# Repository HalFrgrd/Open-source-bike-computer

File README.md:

# Open source-bike-computer
Designs for an open source bike computer.

Similar projects:
- https://github.com/vincent290587/stravaV10
- http://opencyclingcomputer.eu/
- https://gitlab.com/PrzemoF/Open-Cycling-Computer
- https://github.com/hishizuka/pizero_bikecomputer

## BOM

<!--  -->
<!-- |---|---|---|---|---| -->
<!-- |**Preassembled** T-Call v1.3 TTGO ESP32 (no GPS)   | 29 x 7 x 8mm   | $16  | No  |   | -->

||**Item**   | **Dimensions**   | **Cost**  | **Using**  |   |
|---|---|---|---|---|---|
|**Display**|
|| |    | $13   | Yes  |   |
|**Battery and charging**|
||3.7v Lithium Polymer 3200mAh   | 50 x 75 x 7mm  | $8.50  | Yes  |   |
||Receiver pad | 0.5mm thick  | $3  | Yes  |   |
||Charging base  |  | $4  | Yes  |   |
| **Storage** |
||16gb micro SD card   |   | $5  | Yes   |   |
|**Microcontroller and modules** |
||  ESP32 with LiPo charging  |   | $5  | Yes  |   |
|| nrf52840| |$5| Yes||
||  GPS module   |   | $5  | Yes  |   |
||  SIM800L module   |   | $4  | Yes  |   |
|| Micro SD card module  |   | $1  | Yes  |   |
|**Case**|
|| Glass screen protector | | $2 | Yes | |
|| 3D printed enclosure | |  | Yes | |
|| Glue | |  | Yes | |
|| 4 mounting screws | |  | Yes | |
|| 4 threaded heat inserts | |  | Yes | |
|| Rubber o-ring cabling | |  | Yes | |
| **Total** | | | | |

### Actually buying:

[LS027B7DH01](https://www.aliexpress.com/item/33020027250.html?spm=a2g0o.productlist.0.0.36ee3a15mb1GMf&algo_pvid=aad3c1d1-297e-4d29-b040-a34f9ef8f99c&algo_expid=aad3c1d1-297e-4d29-b040-a34f9ef8f99c-1&btsid=0b0a119a15935113972186751eb958&ws_ab_test=searchweb0_0,searchweb201602_,searchweb201603_)
The A indicates maximum of two bright pixels. 
Need an FPC 10 pin connector

## Design

3D printed

The buttons are capacitive pads. 
These pads will be a separate PCB that you can glue onto the 3D printed case.
This will be a water proof seal.
Will the capacitive pads be sensitive to rain?

Maximum target dimensions: 55 wide, 80 long, 20 high 

Need the on off control and charging port to be water proof.

### Capacitive buttons:
ESP32 has 10 capacitive-sensing GPIOs. 
So you don't need to include any extra components to use capacitive buttons
The nrf52 series also don't require any external componenents.

The capacitive pads could perhaps also go under the screen protector.
I'm guessing a screen protector wouldn't reduce the touch sensitivity that much.
This would serve as protection for the capacitive pads.

It is important to reduce the parasitic capacitance and increase the touch capacitance.
How to optimize: reduce trace length by optimizing PCB layout; reduce thickness of the overlay; enlarge electrode's area. 
Could have surface mount pins to reach PCB below.

https://github.com/espressif/esp-iot-solution/blob/master/documents/touch_pad_solution/touch_sensor_design_en.md

https://www.embedded.com/making-capacitive-touch-sensors-water-tolerant/

https://devzone.nordicsemi.com/nordic/short-range-guides/b/design-examples/posts/capacitive-touch-on-the-nrf52-series
### Firmware
https://www.youtube.com/watch?v=lQ157ftTnSs

Google maps platform has a $200 free monthly usage. Could use their route planning.

### Display
[2.42" OLED](https://www.aliexpress.com/item/32950562791.html?spm=a2g0o.productlist.0.0.4f122c2fbCw4XX&algo_pvid=e3eca0d5-b70e-4a4d-96aa-446986a5b739&algo_expid=e3eca0d5-b70e-4a4d-96aa-446986a5b739-2&btsid=0b0a050115931950007767265e4fd4&ws_ab_test=searchweb0_0,searchweb201602_,searchweb201603_)
Not the best choice since they compete with sunlight.

Reflective LCD

https://www.buydisplay.com/blog/what-are-the-main-differences-between-LCD-and-OLED.html

https://www.buydisplay.com/3-4-inch-graphic-touchscreen-lcd-cog-module-240x160-single-sided-fpc
https://www.buydisplay.com/3-inch-touch-240x120-graphic-displays-lcd-serial-interface-black-on-white

https://forum.arduino.cc/index.php?topic=188040.0
https://forum.arduino.cc/index.php?topic=488097.0
https://forum.arduino.cc/index.php?topic=554754.0

Vincent's stravaV10 uses Memory LCD LS027B7DH01
https://makerdyne.com/2015/02/08/large-memory-lcd-breakout-board-details/
https://makerdyne.files.wordpress.com/2015/12/MemoryLCD_Breakout_Board_Schematic.pdf

The LS027B7DH01 with a backlight by Flex:
https://www.digikey.com/products/en?mpart=11103-06_T5&v=2004

### Wireless charging
This both for convenience and keeping the enclosure waterproof. 
Quite cheap for a whole setup. The pad inside of the computer can be very slim.

This one is small enough to be away from antennas.
https://www.mouser.co.uk/ProductDetail/PulseLarsen-Antennas/WMRR124F-2?qs=w%2Fv1CP2dgqrPY4DsgoYlEg%3D%3D

### Contactless payment
https://www.instructables.com/id/RFID-NFC-Tap-and-Go-Ring-for-Credit-Card-Payment/

Could just have a thin slot for a pay as you go card (Revolut or Monzo).Could have SMS notifications so that the bike computer knows when you have paid. 
Set up that sim with that bank card.
Could acetone the bank card to make it slimmer.

### SIM
https://lastminuteengineers.com/sim800l-gsm-module-arduino-tutorial/
I hope to be able to use the microphone pins to play pre-recorded messages.

### PCB design

Pin choice: It seems like the nrf52840 are pretty multi-purpose. For high-frequency stuff, try and avoid pins close to the antenna to avoid interference.
https://devzone.nordicsemi.com/f/nordic-q-a/52857/recommended-pin-usage

P0.0 = 0, P0.1 = 1 .... P0.31 = 31 P1.0 = 32, P1.1 = 33. 

Sharp memory schematics:
https://makerdyne.files.wordpress.com/2015/12/MemoryLCD_Breakout_Board_Schematic.pdf

One set of SPI pins per peripheral: they might work at different speeds. And I think the asynchronous aspect would mean the LCD could be prioritized.

https://github.com/DF4IAH/HFT-Core-Module

Antenna:
SIM868 is L1 band.
Glonass L1: about 1602 MHz
GPS L1: 1575.42 MHz
Beidou: 1575.42 MHz (Possibly lower: 1561.098MHz?)

https://www.antenova.com/integration-hub/antenna-selection-tool/

Drawing antennas as part of the PCB seem like a bad idea. 
They take a lot of testing.

Mouser sells the SR4L049 (both left and right versions) for about 3 dollars. SR4L034 is very similar.

The M20057 and M20047 modules combine the SAW and antenna. Power consumption is about 2ma,

M20047 cost: 4.50 gbp from mouser and at digikey
B3913 cost: 1.62gbp 
SR4L034 cost: 1.44
LNA?:

I'm pretty sure it needs an LNA. So I'm going with 
https://www.u-blox.com/sites/default/files/NEO-8Q-NEO-M8-FW3_HIM_%28UBX-15029985%29.pdf

[Picking a saw filter from Mouser](https://www.mouser.com/pdfdocs/HowToChoosetheOptimalSAWFilter.pdf)

SAW filter: You want something in the middle of the frequencies, so 1588ish and that has a wide enough bandwidth to capture the signals.
Two come up: B3913 and B3413. The B4310 is used in the HFT-Core-Module.
B4310 is from 2015. The B3913 and B3413 are very similar but the B3413 is newer and has improved electrostatic discharge (ESD) robustness. [Qualcomm RF360 website SAW filters for GNSS](https://rffe.qualcomm.com/product/search/automotive/Filters%20for%20GNSS). B4310 doesn't have Beidou next to it on the website. 
I can't find the B3413 in stock, so I'm using the B3913 in stock at digi key.

#### Questions
- The wireless charging setup.
- Battery level indicator.
- Why polarized capacitor in decoupling?
- RF SYNC
- What about low noise ammplifer LNA?

### Case
**Two pcb design**
Have a pcb at the top. 
This has a cut out for the screen.
This top pcb has capacitive buttons.
On the underside of this top pcb, are an on off switch and maybe the usb port. Also could have pressure, temperature, humidity sensor as it should be on the outside? The traces are the link between the outside and the inside.
The 3D printed bottom port of the case could just be unibody.
There would be pcb to pcb connectors.
The top pcb would have surface mounted pins on the underside.
The bottom pcb would have the female connectors.
When you align the pins, the top pcb drops into the bottom one.
[These are pin and socket](https://blog.samtec.com/post/custom-connectors-for-stacking-pcbs/)
There would be o-rings around each of the mounting screws and o-ring cord going around the perimeter.

The two PCBs could fit together inside the 100x100mm size.

Could this extend the ground plane?:
https://blog.antenova.com/how-well-can-an-embedded-antenna-perform-on-a-tiny-pcb

Threaded PCB inserts could provide a flush mounting style.

Connections between plates:
- Ground
- VCC
- Battery switch
- Data+
- Data -
- 5x buttons
- Temperature, pressure, humidity sensor.

Connectors: https://www.samtec.com/products/ftsh

Pins:FTSH-104-01-F-DV
Connector: CLP-104-02-F-D

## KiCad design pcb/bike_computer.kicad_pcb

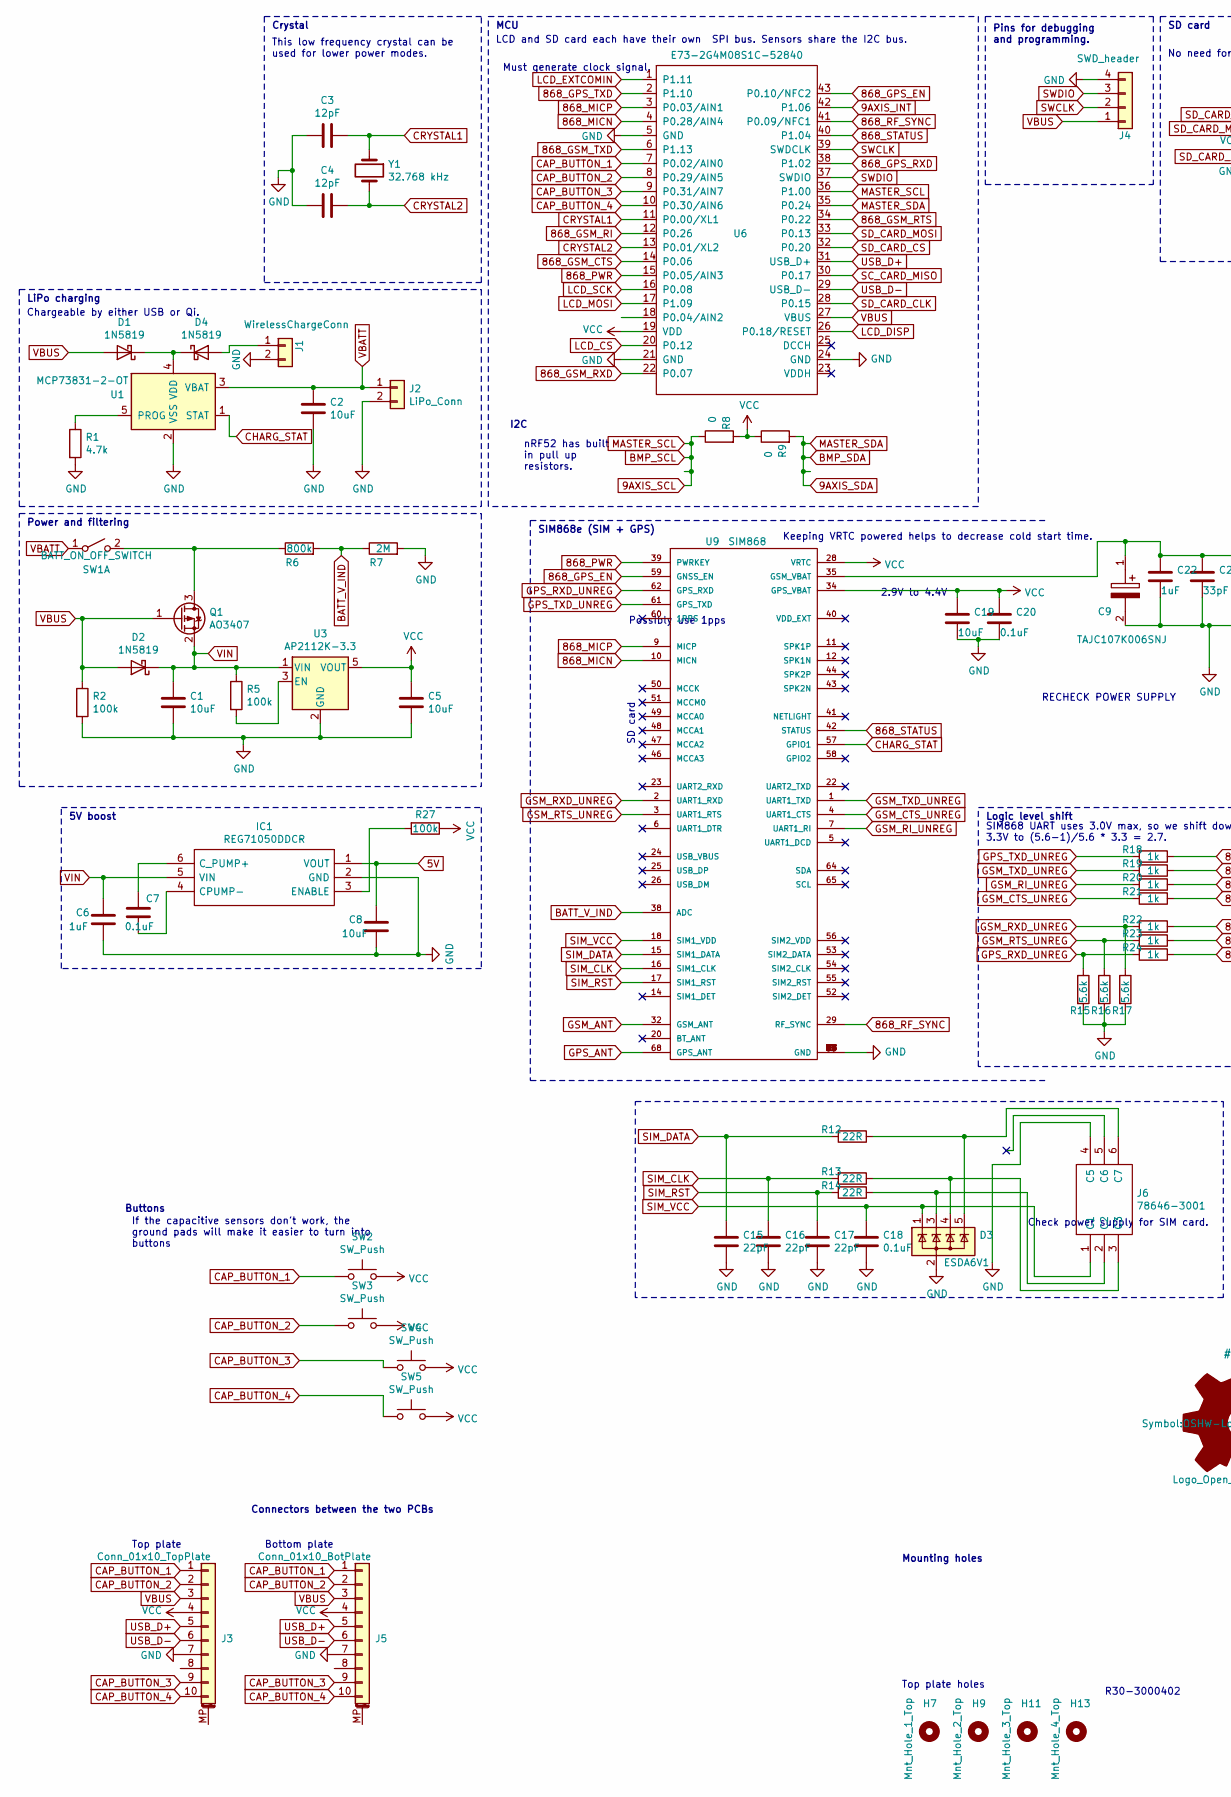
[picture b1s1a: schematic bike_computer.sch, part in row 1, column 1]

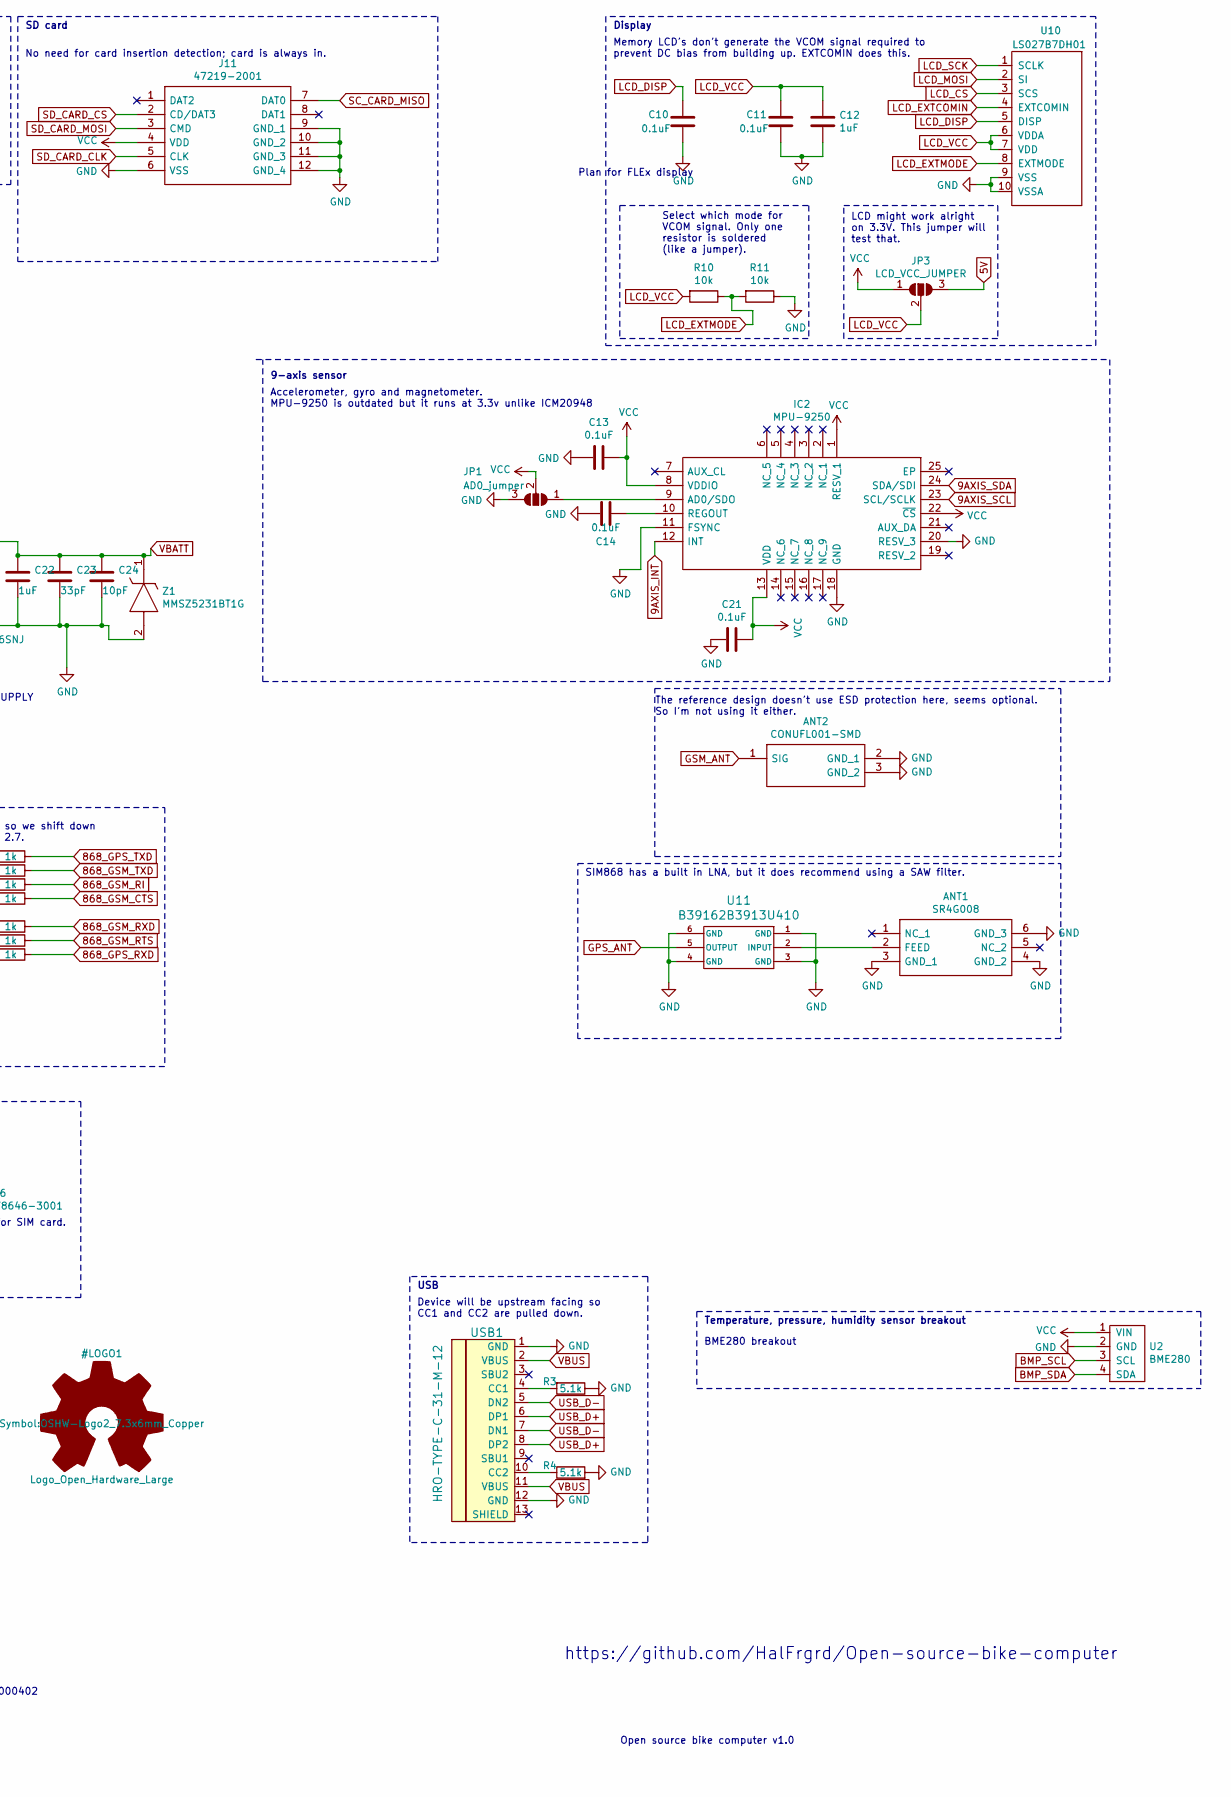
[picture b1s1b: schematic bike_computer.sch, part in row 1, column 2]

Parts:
ANT1: SR4G008; Mouser Part Number 237-SR4G008
ANT2: CONUFL001-SMD; Mouser Part Number 712-CONUFL001-SMD
C1, C2, C5, C8, C19: 10uF; 1206_0603_hand_solder
C3, C4: 12pF; 1206_0603_hand_solder
C6, C12, C22: 1uF; 1206_0603_hand_solder
C7, C10, C11, C13, C14, C18, C20, C21: 0.1uF; 1206_0603_hand_solder
C9: TAJC107K006SNJ; CAPPM6032X280N; Mouser Part Number 581-TAJC107K006SNJ
C15, C16, C17: 22pF; 1206_0603_hand_solder
C23: 33pF; 1206_0603_hand_solder
C24: 10pF; 1206_0603_hand_solder
D1, D2, D4: 1N5819; D_SOD-123
D3: ESDA6V1; SOT95P280X145-6N
H7: Mnt_Hole_1_Top; R303000402
H9: Mnt_Hole_2_Top; R303000402
H11: Mnt_Hole_3_Top; R303000402
H13: Mnt_Hole_4_Top; R303000402
IC1: REG71050DDCR; SOT95P280X110-6N; Mouser Part Number 595-REG71050DDCR
IC2: MPU-9250; QFN40P300X300X105-25N-D; Mouser Part Number 410-MPU-9250
J1: WirelessChargeConn; PinHeader_1x02_P1.27mm_Vertical
J2: LiPo_Conn; PinHeader_1x02_P1.27mm_Vertical
J3: Conn_01x10_TopPlate; 10_smd_connector
J4: SWD_header; PinHeader_1x04_P2.54mm_Vertical
J5: Conn_01x10_BotPlate; PinHeader_1x10_P2.54mm_Vertical
J6: 78646-3001; Mouser Part Number 538-78646-3001
J11: 47219-2001; 472192001; Mouser Part Number 538-47219-2001
JP1: AD0_jumper; SolderJumper-3_P1.3mm_Open_RoundedPad1.0x1.5mm
JP3: LCD_VCC_JUMPER; SolderJumper-3_P1.3mm_Open_RoundedPad1.0x1.5mm
Q1: AO3407; SOT-23
R1: 4.7k; 1206_0603_hand_solder
R2, R5, R27: 100k; 1206_0603_hand_solder
R3, R4: 5.1k; 1206_0603_hand_solder
R6: 800k; 1206_0603_hand_solder
R7: 2M; 1206_0603_hand_solder
R8, R9: 0; 1206_0603_hand_solder
R10, R11: 10k; 1206_0603_hand_solder
R12, R13, R14: 22R; 1206_0603_hand_solder
R15, R16, R17: 5.6k; 1206_0603_hand_solder
R18, R19, R20, R21, R22, R23, R24: 1k; 1206_0603_hand_solder
SW1: BATT_ON_OFF_SWITCH; switch_MSK-12C02_smd
SW2, SW3, SW4, SW5: SW_Push; KSC521JROHS_with_pad
U1: MCP73831-2-OT; SOT-23-5
U2: BME280
U3: AP2112K-3.3; SOT-23-5
U6: E73-2G4M08S1C-52840
U9: SIM868; XCVR_SIM868
U10: LS027B7DH01; TE_1-1734839-0_1x10-1MP_P0.5mm_Horizontal
U11: B39162B3913U410
USB1: HRO-TYPE-C-31-M-12
Y1: 32.768 kHz; Crystal_DS26_D2.0mm_L6.0mm_Horizontal
Z1: MMSZ5231BT1G; SOD3716X135N; Mouser Part Number 863-MMSZ5231BT1G

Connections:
5V: C8.1, IC1.1 (VOUT), JP3.3 (B)
9AXIS_INT: IC2.12 (INT), U6.42 (P1.06)
9AXIS_SCL: IC2.23 (SCL/SCLK), R8.1, U2.3 (SCL), U6.36 (P1.00)
9AXIS_SDA: IC2.24 (SDA/SDI), R9.2, U2.4 (SDA), U6.35 (P0.24)
868_GPS_EN: U6.43 (P0.10/NFC2), U9.59 (GNSS_EN)
868_GPS_RXD: R24.1, U6.38 (P1.02)
868_GPS_TXD: R18.1, U6.2 (P1.10)
868_GSM_CTS: R21.1, U6.14 (P0.06)
868_GSM_RI: R20.1, U6.12 (P0.26)
868_GSM_RTS: R23.1, U6.34 (P0.22)
868_GSM_RXD: R22.1, U6.22 (P0.07)
868_GSM_TXD: R19.1, U6.6 (P1.13)
868_MICN: U6.4 (P0.28/AIN4), U9.10 (MICN)
868_MICP: U6.3 (P0.03/AIN1), U9.9 (MICP)
868_PWR: U6.15 (P0.05/AIN3), U9.39 (PWRKEY)
868_RF_SYNC: U6.41 (P0.09/NFC1), U9.29 (RF_SYNC)
868_STATUS: U6.40 (P1.04), U9.42 (STATUS)
BATT_V_IND: R6.2, R7.1, U9.38 (ADC)
CAP_BUTTON_1: J3.1, J5.1, SW2.1, U6.7 (P0.02/AIN0)
CAP_BUTTON_2: J3.2, J5.2, SW3.1, U6.8 (P0.29/AIN5)
CAP_BUTTON_3: J3.9, J5.9, SW4.1, U6.9 (P0.31/AIN7)
CAP_BUTTON_4: J3.10, J5.10, SW5.1, U6.10 (P0.30/AIN6)
CHARG_STAT: U1.1 (STAT), U9.57 (GPIO1)
CRYSTAL1: C3.1, U6.11 (P0.00/XL1), Y1.1
CRYSTAL2: C4.1, U6.13 (P0.01/XL2), Y1.2
GND: ANT1.3 (GND_1), ANT1.4 (GND_2), ANT1.6 (GND_3), ANT2.2 (GND_1), ANT2.3 (GND_2), C1.2, C2.2, C3.2, C4.2, C5.2, C6.2, C8.2, C9.2, C10.2, C11.2, C12.2, C13.2, C14.1, C15.2, C16.2, C17.2, C18.2, C19.2, C20.2, C21.2, C22.2, C23.2, C24.2, D3.2 (A), IC1.2 (GND), IC2.11 (FSYNC), IC2.18 (GND), IC2.20 (RESV_3), J1.2, J2.2, J3.7, J4.4, J5.7, J6.4 (C5), J11.6 (VSS), J11.9 (GND_1), J11.10 (GND_2), J11.11 (GND_3), J11.12 (GND_4), JP1.3 (B), R1.2, R2.2, R3.1, R4.2, R7.2, R11.1, R15.2, R16.2, R17.2, U1.2 (VSS), U2.2 (GND), U3.2 (GND), U6.5 (GND), U6.21 (GND), U6.24 (GND), U9.8 (GND), U9.13 (GND), U9.19 (GND), U9.21 (GND), U9.27 (GND), U9.30 (GND), U9.31 (GND), U9.33 (GND), U9.36 (GND), U9.37 (GND), U9.45 (GND), U9.63 (GND), U9.66 (GND), U9.67 (GND), U9.69 (GND), U9.70 (GND), U9.71 (GND), U9.72 (GND), U9.73 (GND), U9.74 (GND), U9.75 (GND), U9.76 (GND), U9.77 (GND), U10.9 (VSS), U10.10 (VSSA), U11.1 (GND), U11.3 (GND), U11.4 (GND), U11.6 (GND), USB1.1 (GND), USB1.12 (GND), Z1.2
GPS_ANT: U9.68 (GPS_ANT), U11.5 (OUTPUT)
GPS_RXD_UNREG: R15.1, R24.2, U9.62 (GPS_RXD)
GPS_TXD_UNREG: R18.2, U9.61 (GPS_TXD)
GSM_ANT: ANT2.1 (SIG), U9.32 (GSM_ANT)
GSM_CTS_UNREG: R21.2, U9.4 (UART1_CTS)
GSM_RI_UNREG: R20.2, U9.7 (UART1_RI)
GSM_RTS_UNREG: R16.1, R23.2, U9.3 (UART1_RTS)
GSM_RXD_UNREG: R17.1, R22.2, U9.2 (UART1_RXD)
GSM_TXD_UNREG: R19.2, U9.1 (UART1_TXD)
LCD_CS: U6.20 (P0.12), U10.3 (SCS)
LCD_DISP: C10.1, U6.26 (P0.18/RESET), U10.5 (DISP)
LCD_EXTCOMIN: U6.1 (P1.11), U10.4 (EXTCOMIN)
LCD_EXTMODE: R10.1, R11.2, U10.8 (EXTMODE)
LCD_MOSI: U6.17 (P1.09), U10.2 (SI)
LCD_SCK: U6.16 (P0.08), U10.1 (SCLK)
LCD_VCC: C11.1, C12.1, JP3.2 (C), R10.2, U10.6 (VDDA), U10.7 (VDD)
unnamed: ANT1.2 (FEED), U11.2 (INPUT)
unnamed: C7.1, IC1.6 (C_PUMP+)
unnamed: C7.2, IC1.4 (CPUMP-)
unnamed: C14.2, IC2.10 (REGOUT)
unnamed: D1.1 (K), D4.1 (K), U1.4 (VDD)
unnamed: D3.3 (K), J6.2 (C2), R14.1
unnamed: D3.4 (K), J6.3 (C3), R13.1
unnamed: D3.5 (K), J6.6 (C7), R12.1
unnamed: D4.2 (A), J1.1
unnamed: IC1.3 (ENABLE), R27.2
unnamed: IC2.9 (AD0/SDO), JP1.1 (A)
unnamed: Q1.3 (D), R6.1, SW1.2 (B)
unnamed: R1.1, U1.5 (PROG)
unnamed: R3.2, USB1.4 (CC1)
unnamed: R4.1, USB1.10 (CC2)
unnamed: R5.2, U3.3 (EN)
SC_CARD_MISO: J11.7 (DAT0), U6.30 (P0.17)
SD_CARD_CLK: J11.5 (CLK), U6.28 (P0.15)
SD_CARD_CS: J11.2 (CD/DAT3), U6.32 (P0.20)
SD_CARD_MOSI: J11.3 (CMD), U6.33 (P0.13)
SIM_CLK: C16.1, R13.2, U9.16 (SIM1_CLK)
SIM_DATA: C15.1, R12.2, U9.15 (SIM1_DATA)
SIM_RST: C17.1, R14.2, U9.17 (SIM1_RST)
SIM_VCC: C18.1, D3.1 (K), J6.1 (C1), U9.18 (SIM1_VDD)
SWCLK: J4.2, U6.39 (SWDCLK)
SWDIO: J4.3, U6.37 (SWDIO)
USB_D+: J3.5, J5.5, U6.31 (USB_D+), USB1.6 (DP1), USB1.8 (DP2)
USB_D-: J3.6, J5.6, U6.29 (USB_D-), USB1.5 (DN2), USB1.7 (DN1)
VBATT: C2.1, C9.1, C22.1, C23.1, C24.1, J2.1, SW1.1 (A), U1.3 (VBAT), U9.35 (GSM_VBAT), Z1.1
VBUS: D1.2 (A), D2.2 (A), J3.3, J4.1, J5.3, Q1.1 (G), R2.1, U6.27 (VBUS), USB1.2 (VBUS), USB1.11 (VBUS)
VCC: C5.1, C13.1, C19.1, C20.1, C21.1, IC2.1 (RESV_1), IC2.8 (VDDIO), IC2.13 (VDD), IC2.22 (~CS), J3.4, J5.4, J11.4 (VDD), JP1.2 (C), JP3.1 (A), R8.2, R9.1, R27.1, SW2.2, SW3.2, SW4.2, SW5.2, U2.1 (VIN), U3.5 (VOUT), U6.19 (VDD), U9.28 (VRTC), U9.34 (GPS_VBAT)
VIN: C1.1, C6.1, D2.1 (K), IC1.5 (VIN), Q1.2 (S), R5.1, U3.1 (VIN)

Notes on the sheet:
MCU
Power and filtering
LiPo charging
USB
SD card
Memory LCD's don't generate the VCOM signal required to prevent DC bias from building up. EXTCOMIN does this.
Display
Select which mode for VCOM signal. Only one resistor is soldered (like a jumper).
Device will be upstream facing so CC1 and CC2 are pulled down.
This low frequency crystal can be used for lower power modes.
Crystal
LCD might work alright on 3.3V. This jumper will test that.
No need for card insertion detection; card is always in.
9-axis sensor
Pins for debugging and programming.
BME280 breakout
I2C
nRF52 has built in pull up resistors.
Temperature, pressure, humidity sensor breakout
Buttons
5V boost
https://github.com/HalFrgrd/Open-source-bike-computer
Open source bike computer v1.0
LCD and SD card each have their own SPI bus. Sensors share the I2C bus.
If the capacitive sensors don't work, the ground pads will make it easier to turn into buttons
Accelerometer, gyro and magnetometer. MPU-9250 is outdated but it runs at 3.3v unlike ICM20948
Chargeable by either USB or Qi.
SIM868e (SIM + GPS)
Keeping VRTC powered helps to decrease cold start time.
SD card
Possibly use 1pps
Check power supply for SIM card.
SIM868 UART uses 3.0V max, so we shift down 3.3V to (5.6-1)/5.6 * 3.3 = 2.7.
Logic level shift
Must generate clock signal.
Plan for FLEx display
SIM868 has a built in LNA, but it does recommend using a SAW filter.
2.9V to 4.4V
RECHECK POWER SUPPLY
Connectors between the two PCBs

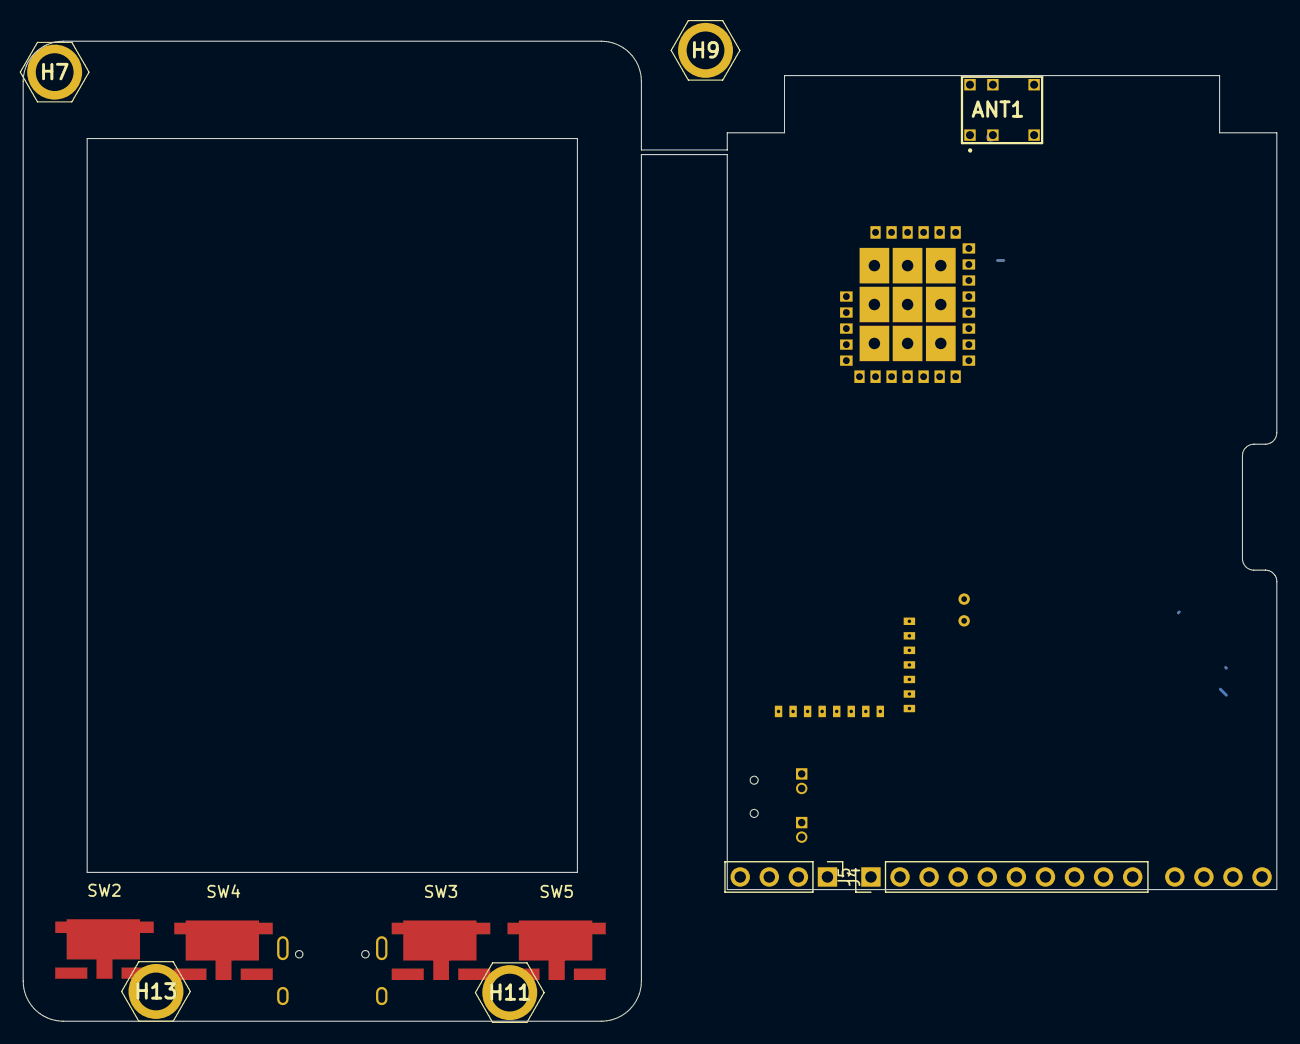
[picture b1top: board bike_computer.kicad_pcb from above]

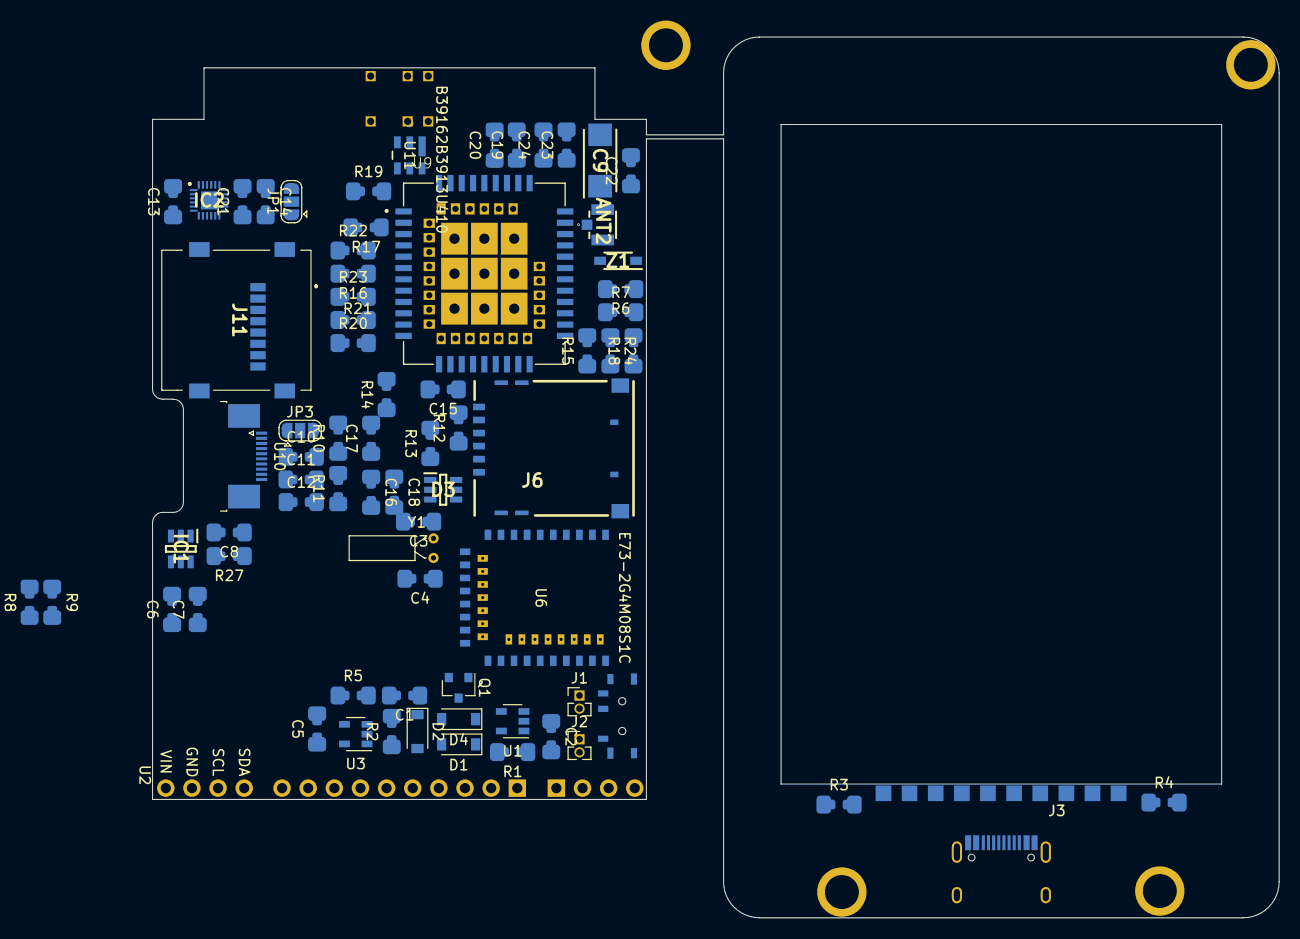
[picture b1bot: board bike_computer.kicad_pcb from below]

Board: 2 copper layers, 109.5 x 85.6 mm, 86 parts (75 on the bottom side), 74 nets.

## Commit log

2020-06-26 Planning design
2020-06-27 Added more details
2020-06-28 Working on a pcb
2020-06-28 Working on schematic
2020-06-30 worked on schematic
2020-06-30 Assigning footprints
2020-07-02 Sorting out 2 plate design
2020-07-04 Sorted main layout

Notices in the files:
parts and their libraries:
Copyright 2016 Accelerated Designs. All rights reserved.
